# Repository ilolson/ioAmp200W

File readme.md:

# ioAmp200W

Small but powerful USB-C powered two channel speaker amplifier.

# Summary

Integrating the MA5332MS from infineon, a super efficient and compact 2 channel class D amplifier. With a TLV320AIC3254 mini DSP, a low power and compact DSP for consumer audio applications that will allow for tight integration. TPS26750 to control USB PD 3.1 EPR power supplies for up to 240W of DC power. An easy to use RP2350 microcontroller for high level control of the system, and hopefully digital audio in at 24bit/96khz.

The goal is to design a compact and efficient circuit board that can supply a wide range of power to the class D amplifier through USB-C Power Delivery. It will include line in and out for easy audio amplification. Including a quality and easy to use DSP such as the TLV320AIC3254 mini DSP should allow us to explore signal processing techniques to achieve optimal results at different power supply voltages, and different speaker setups. Digital audio in over USB-C should be possible in the future with the RP2350 and the DSP. For fun we can drive a HUB75 matrix panel in real time using existing optimized libraries with our signal.

# Power Supply

The USB PD 3.1 EPR can supply a maximum of 48V@5A for 240 watts DC. Even lower settings such as 20V/3A is a common laptop charging standard and many people already own USB-C bricks that can supply this which should be enough for some decent audio output, it also won't damage anything so it will be a safe default. The highest easily available is 28V@5A for 140W DC. 48V@5A is hard to find and expensive although I do plan on testing it on the first revision. 

# Major Circuits

-RP2350 microcontroller

-TI TPS26750 PD 3.1 EPR controller and power management system

-MA5332MS class D amplifier (up to 100W/Ch without heatsink)

-TLV3254AIC3254 low power consumer audio codec DSP, digital input from RP2350 and analog line in

# Highlights

-USB-C digital audio in (24 bit/96kHz)

-Program/Serial connectivity available while streaming audio over USB for easy real time DSP control

-Line In

-HUB75 interface (for driving LED matrix panels)

-High quality audio amplification at a manageable cost for DIY setups

-Wide range of easily available power supplies

# Status

-Initial schematic design

-Compilable firmware, serial and digital audio in working

-Auto install toolchain and compile scripts

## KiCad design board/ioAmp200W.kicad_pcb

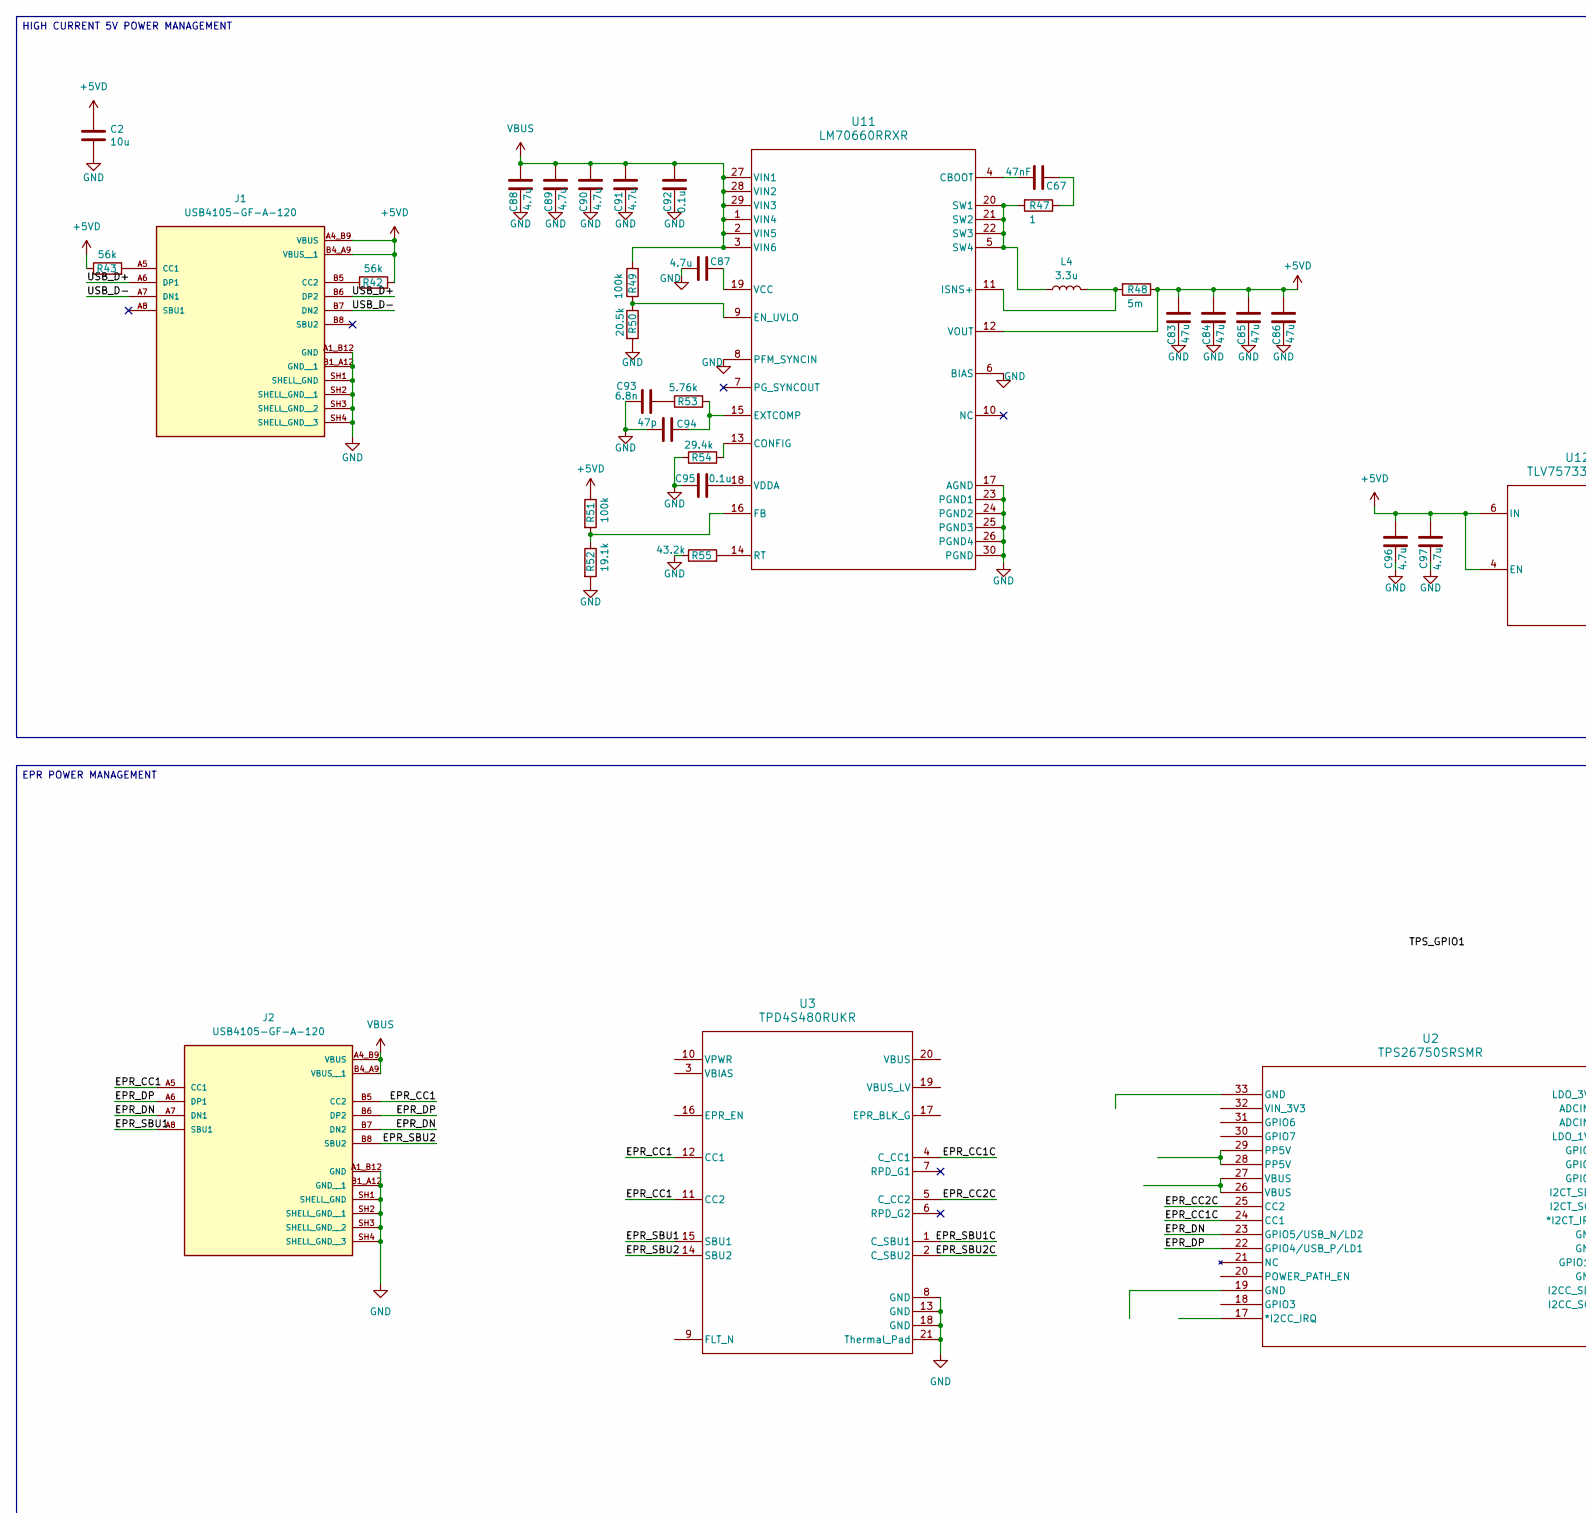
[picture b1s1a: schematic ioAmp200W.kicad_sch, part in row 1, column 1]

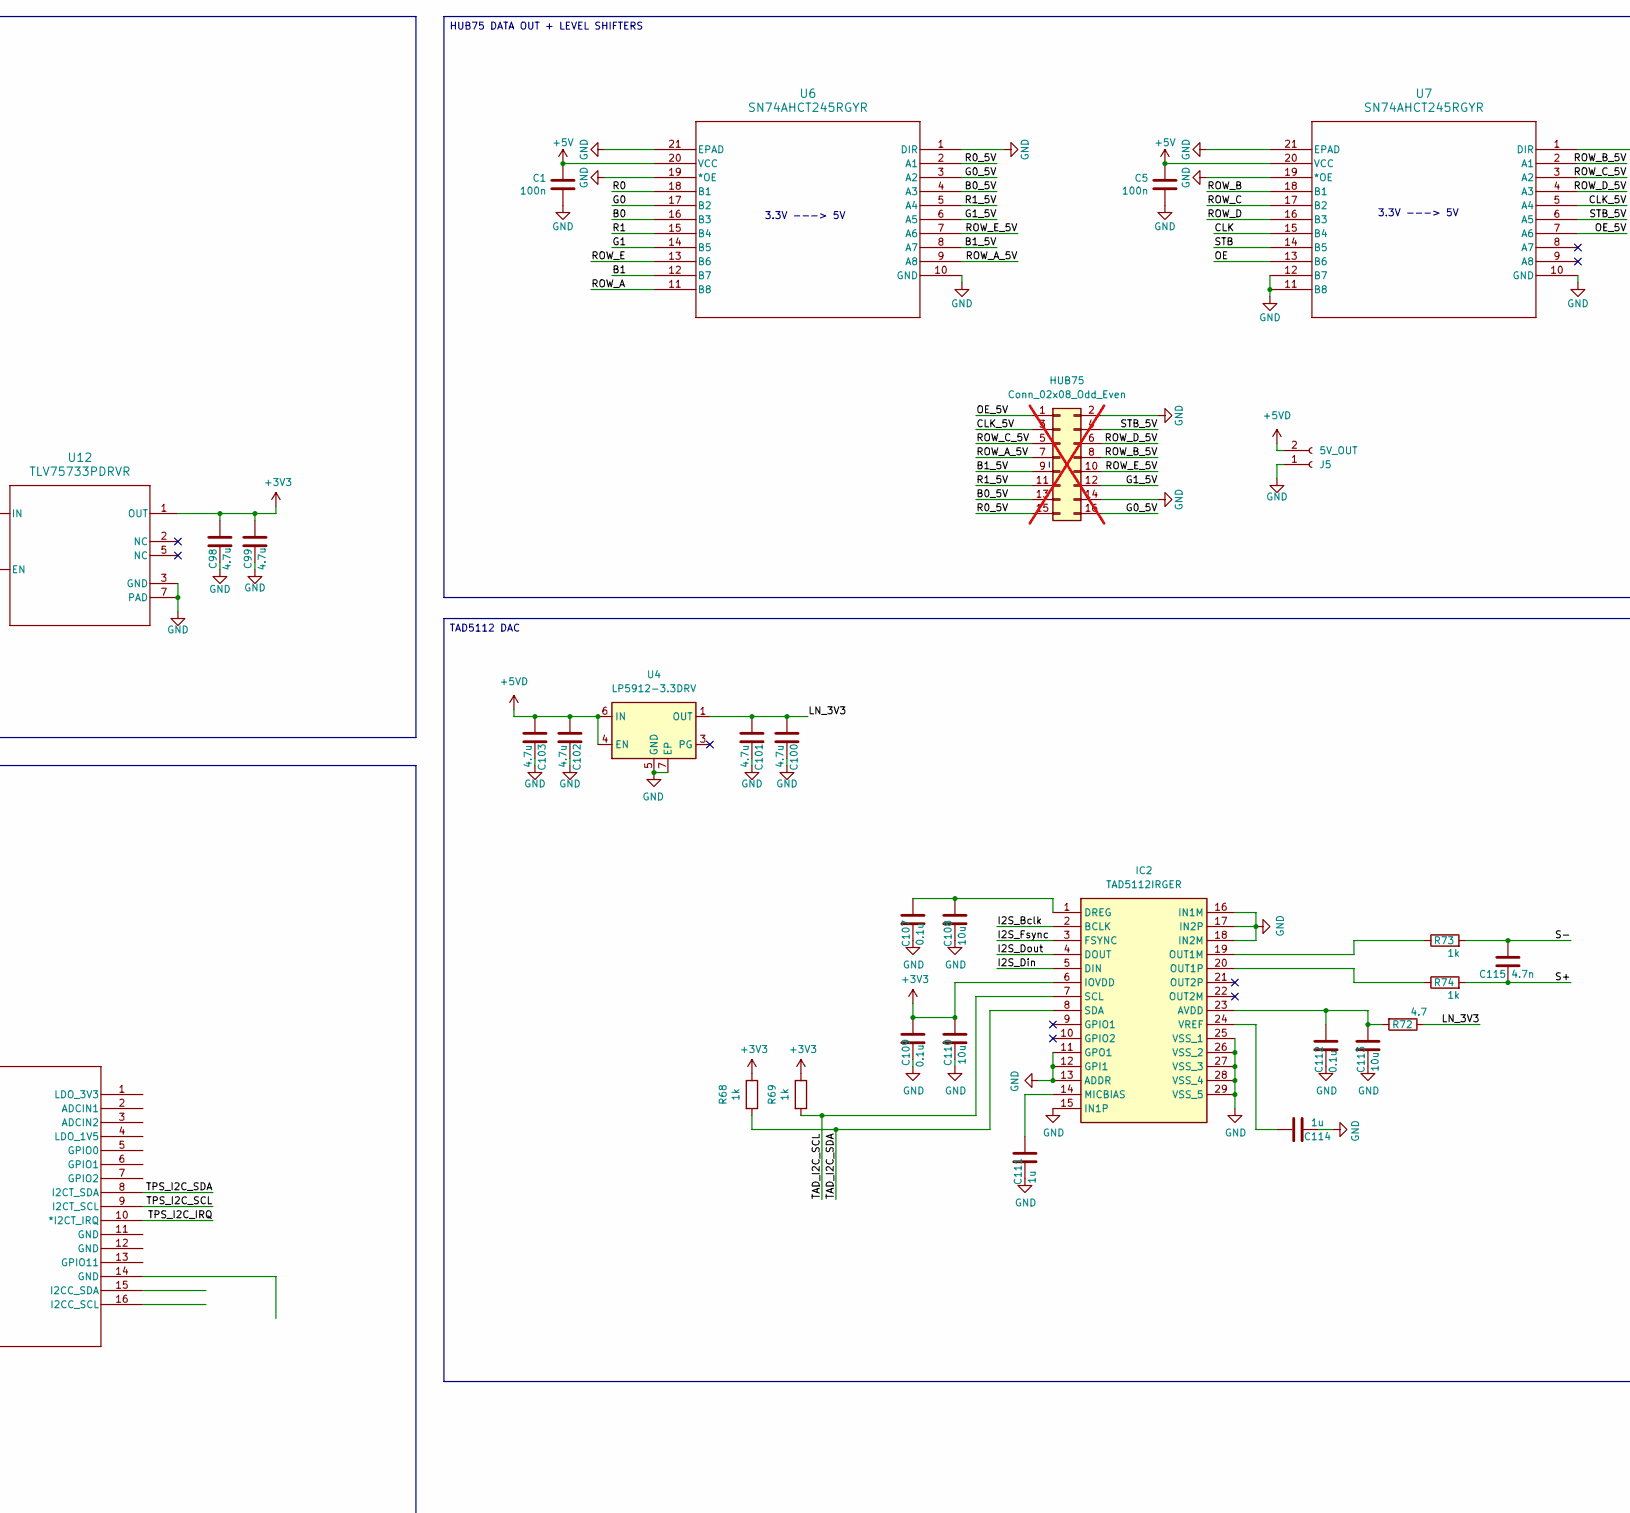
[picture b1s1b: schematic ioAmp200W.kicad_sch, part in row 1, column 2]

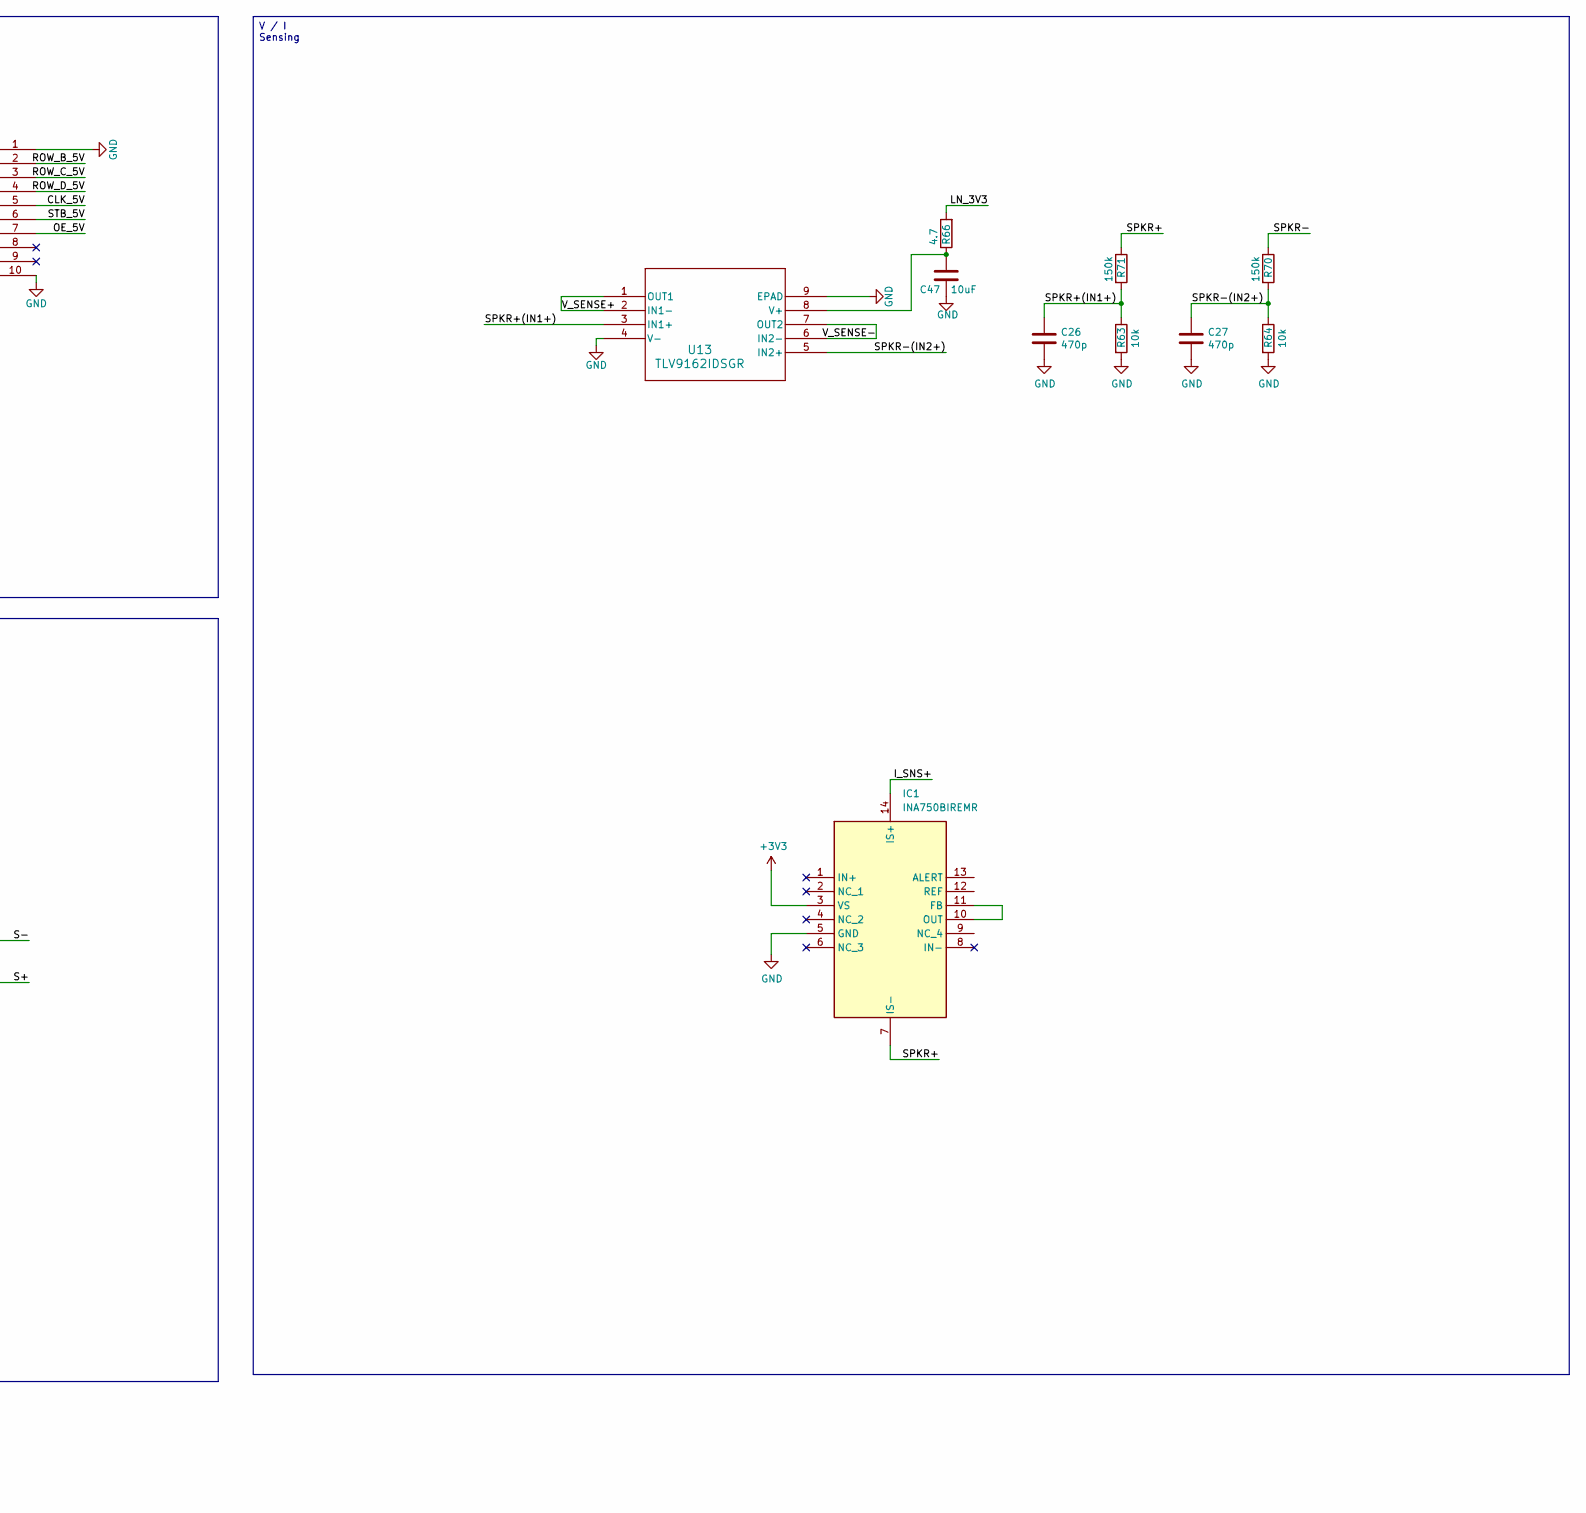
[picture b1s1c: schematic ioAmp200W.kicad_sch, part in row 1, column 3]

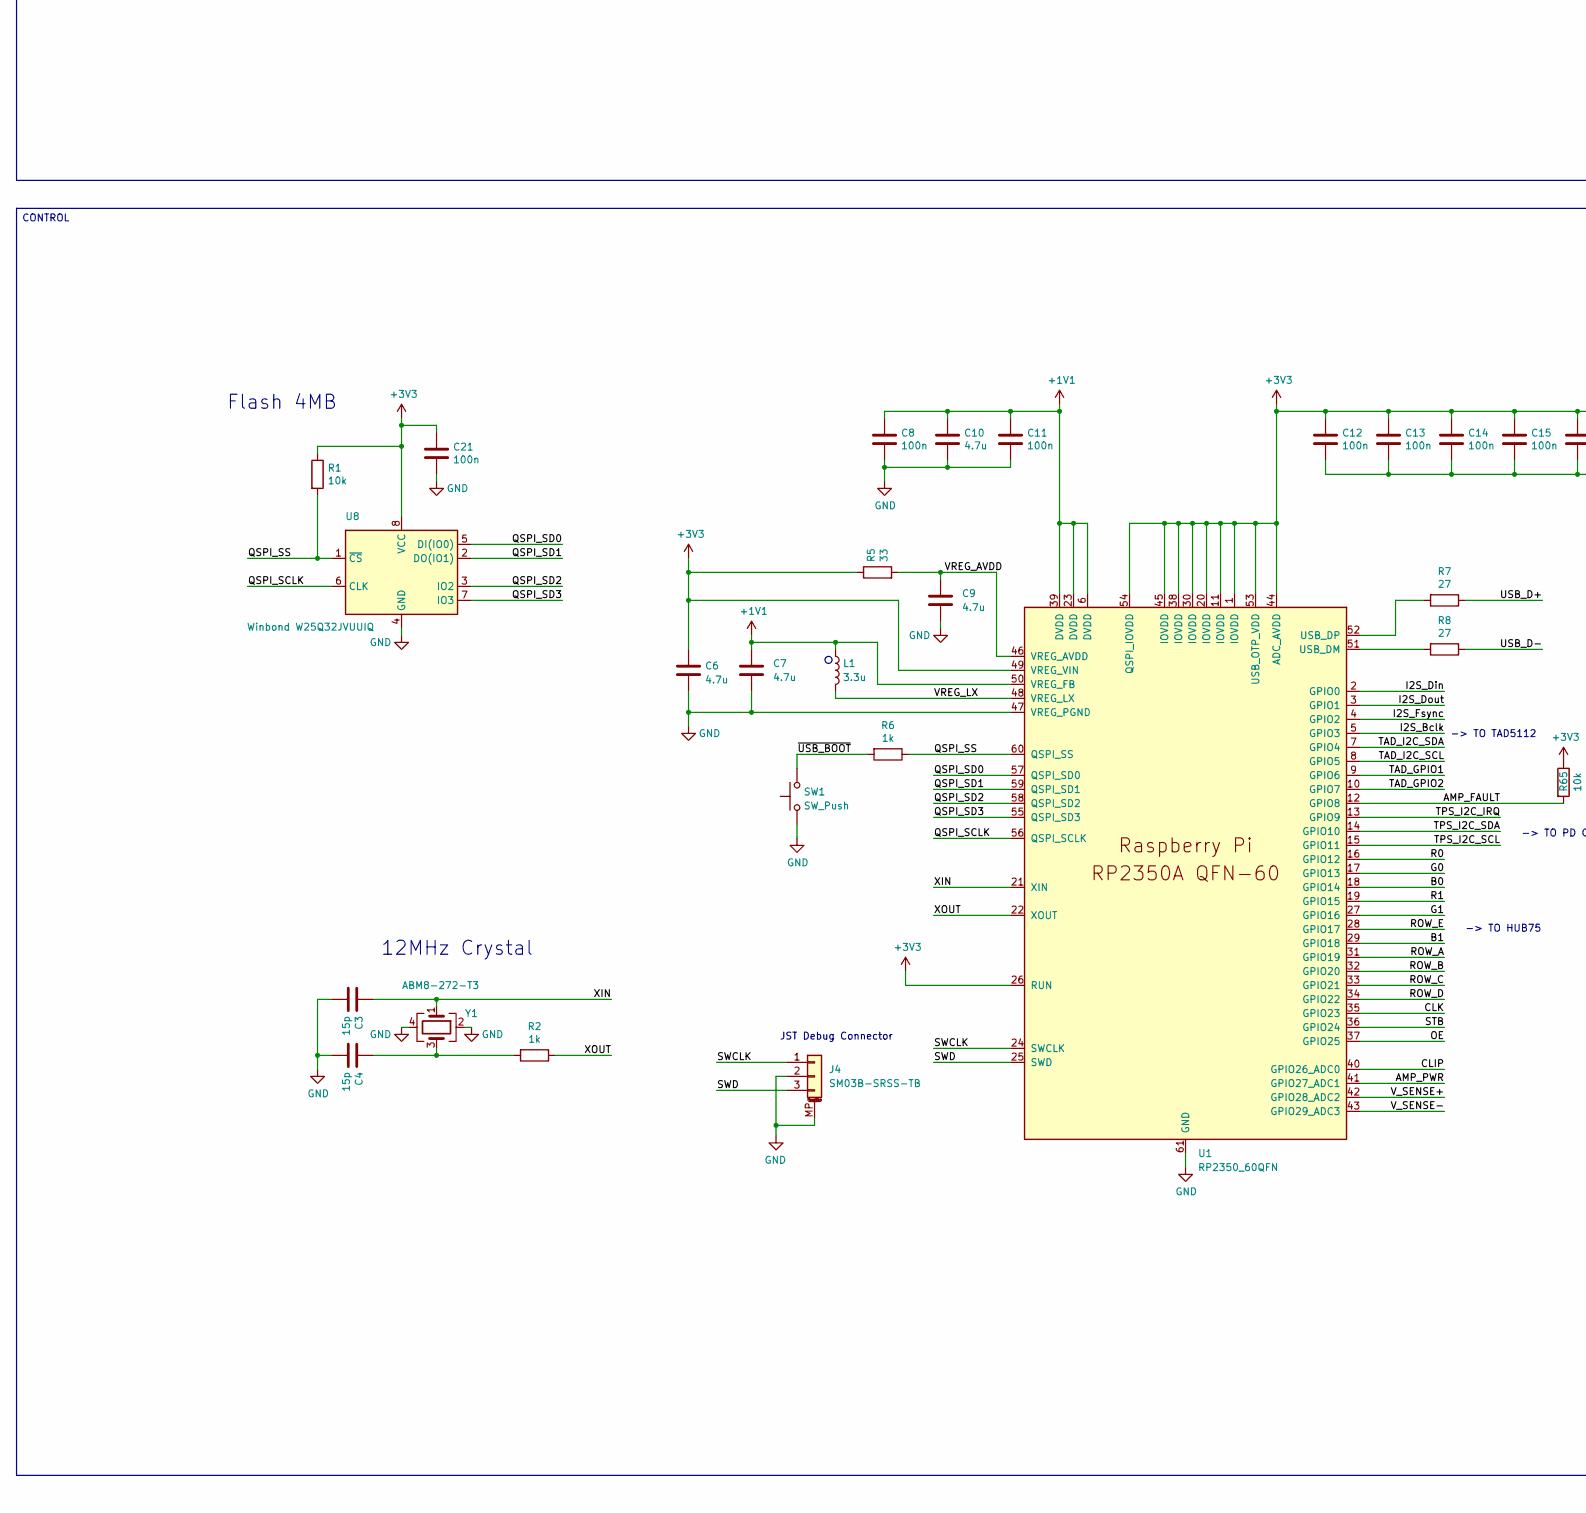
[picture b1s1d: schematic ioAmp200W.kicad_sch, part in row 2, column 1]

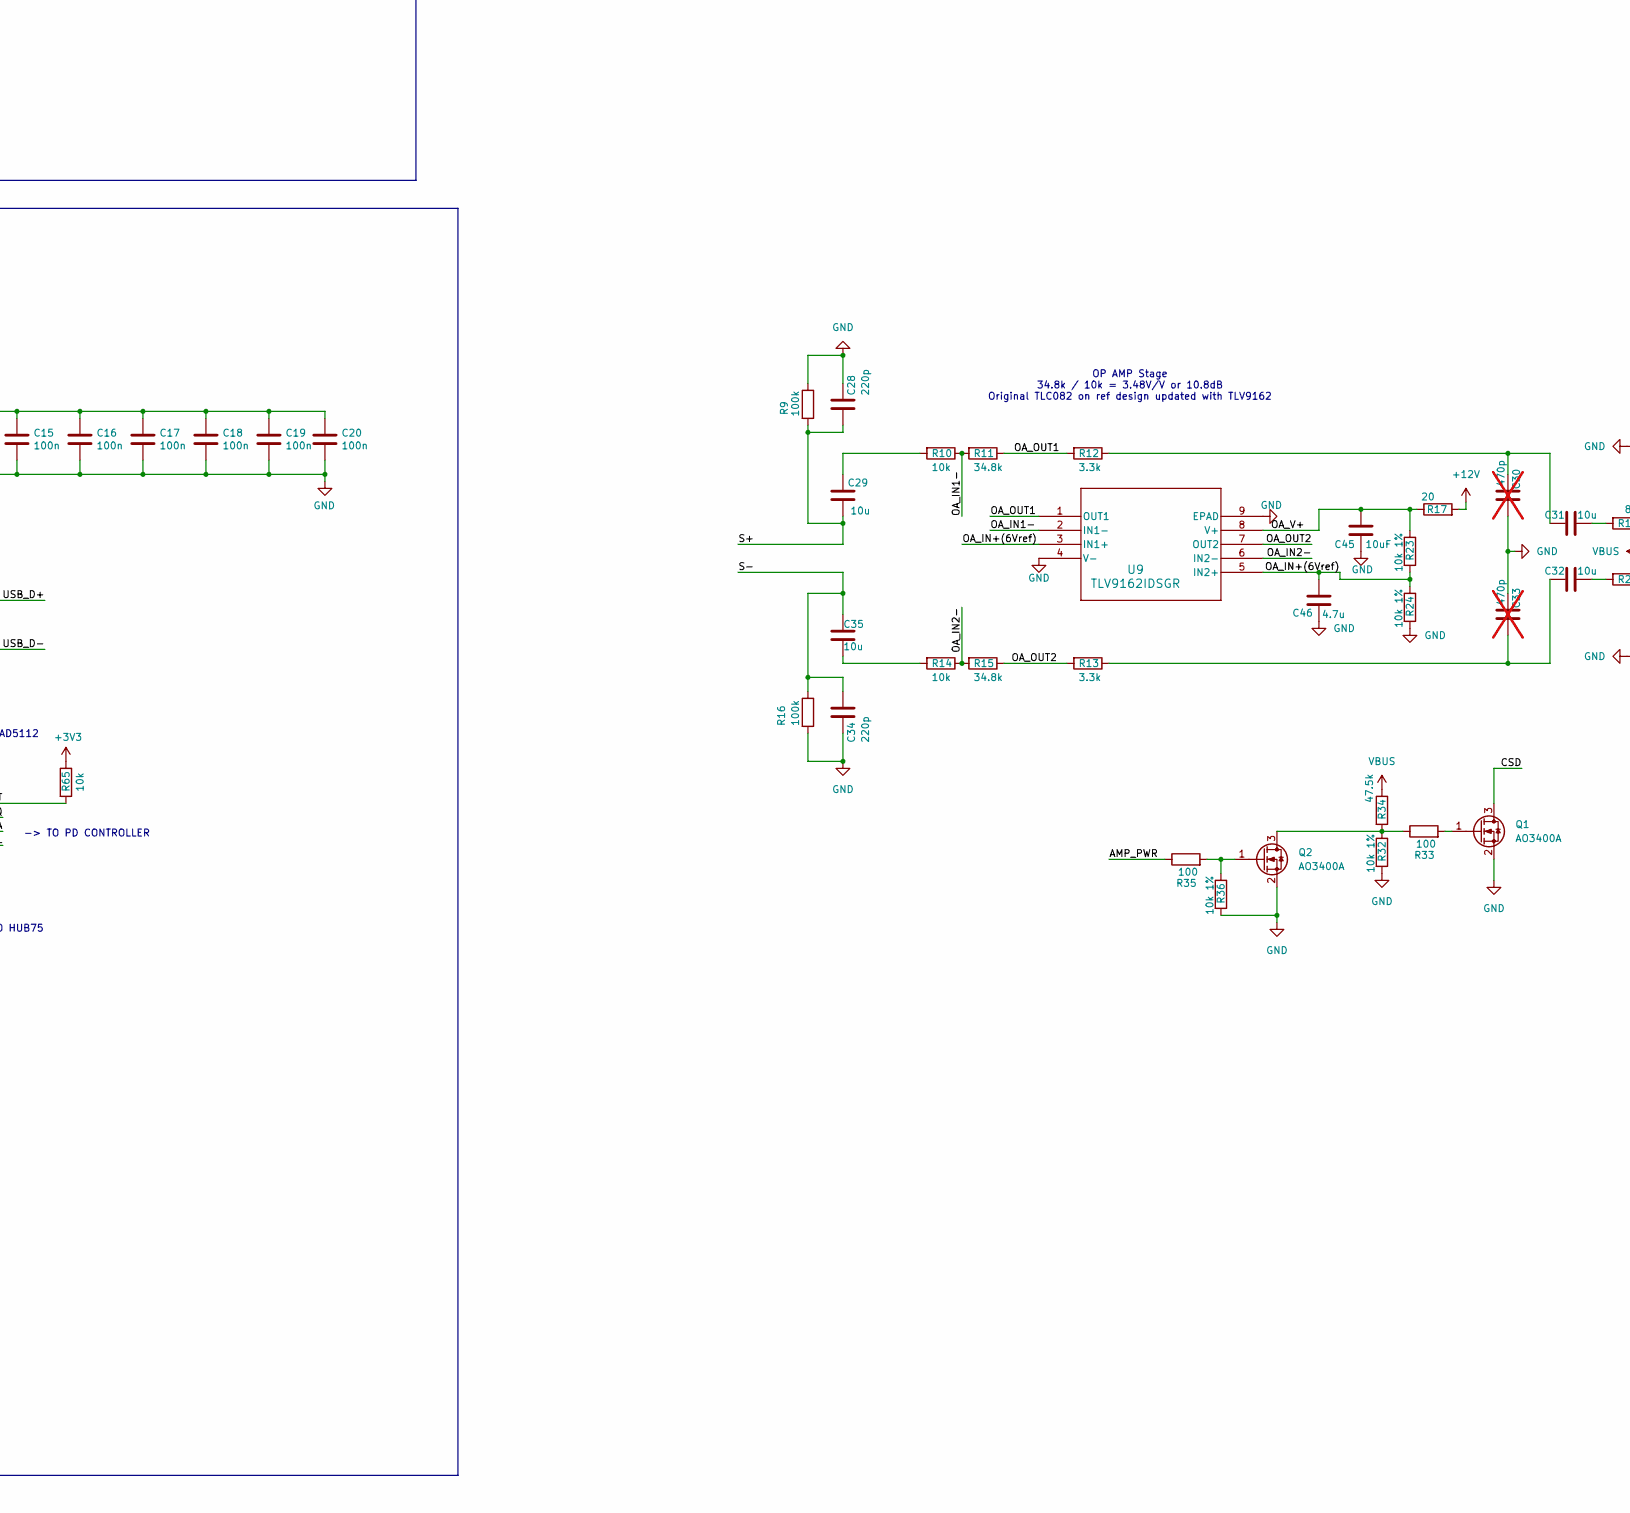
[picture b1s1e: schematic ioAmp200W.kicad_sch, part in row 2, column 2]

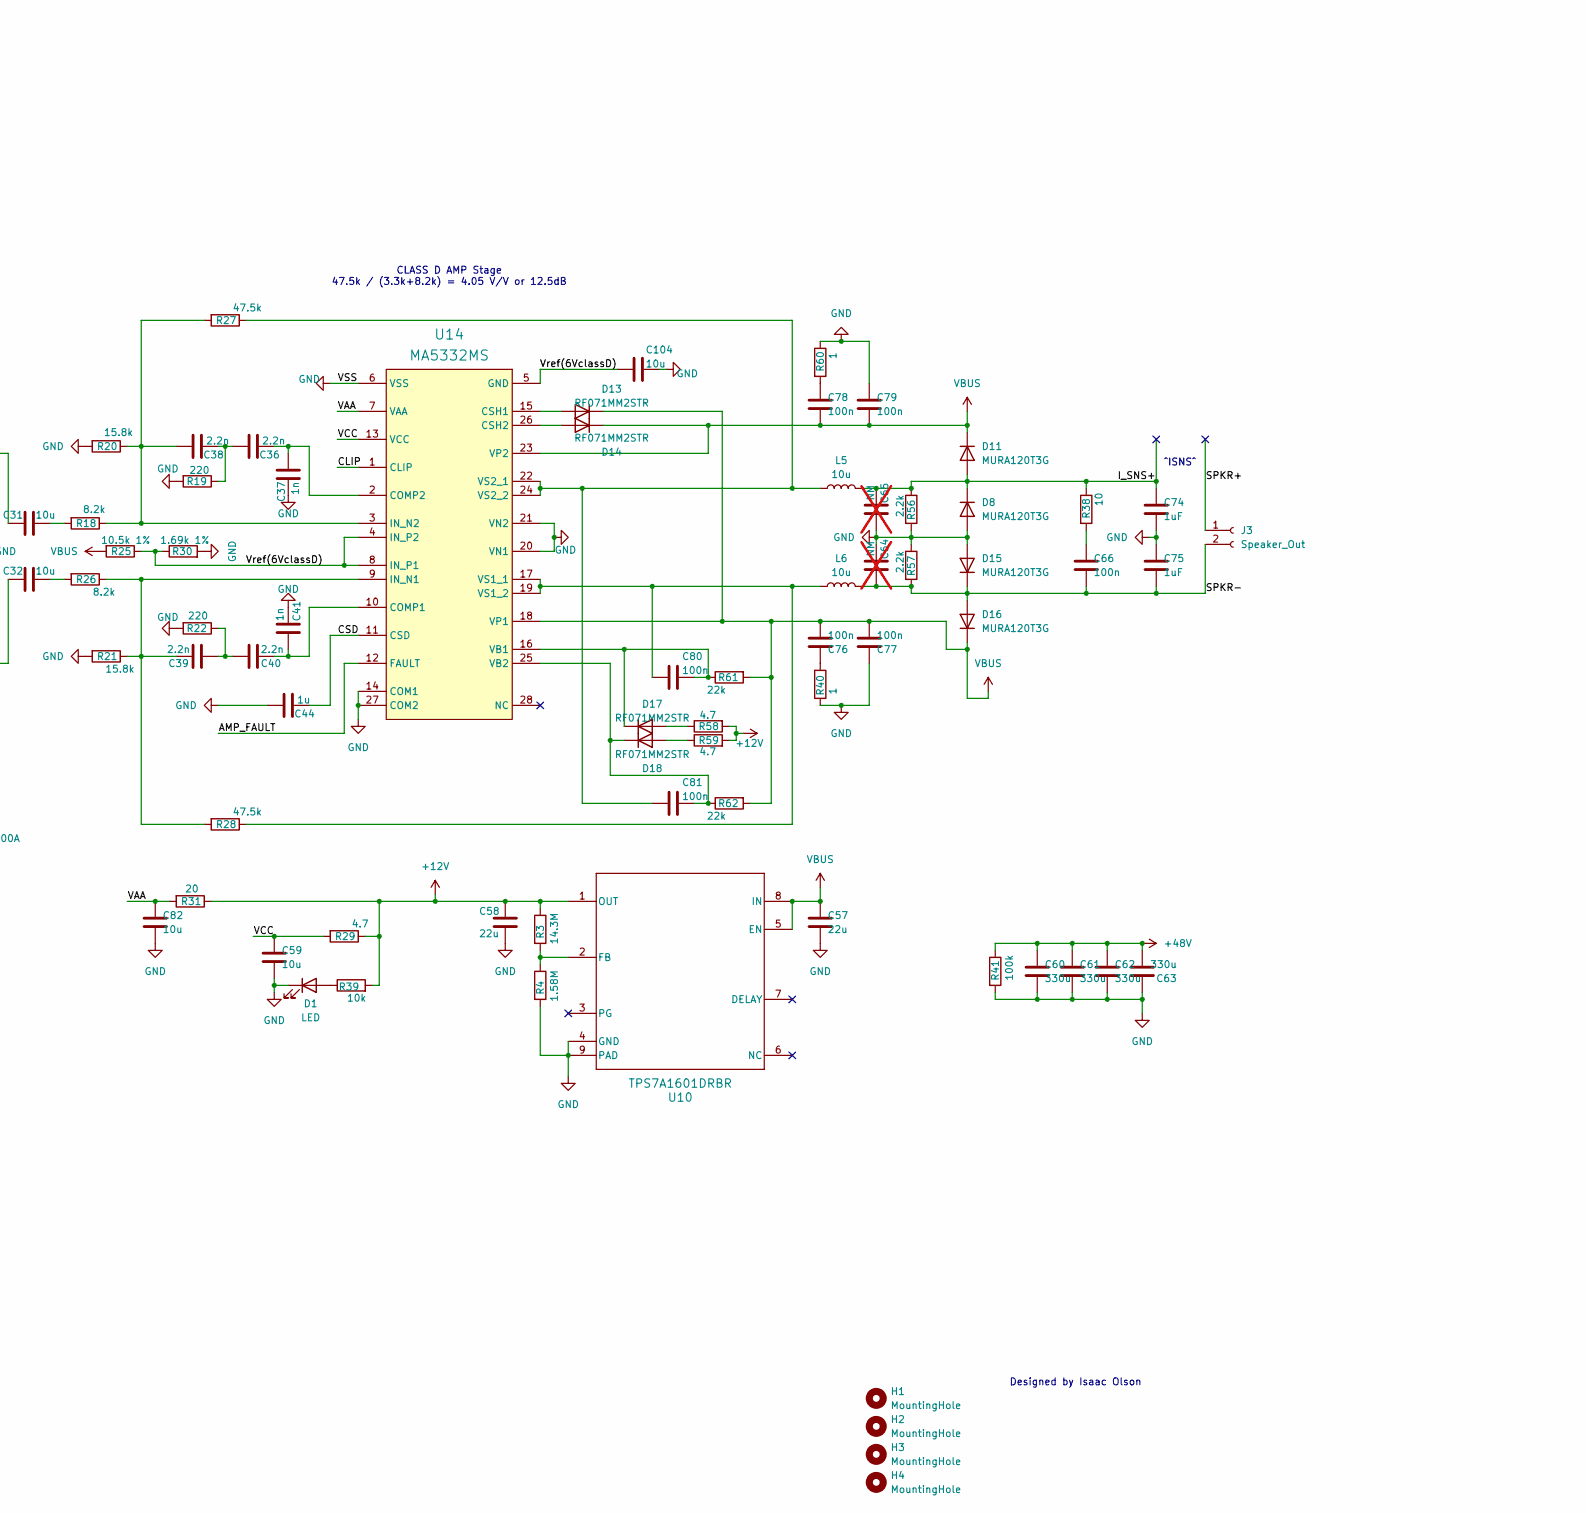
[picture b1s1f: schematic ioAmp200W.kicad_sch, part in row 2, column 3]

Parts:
C1, C5, C8, C11, C12, C13, C14, C15, C16, C17, C18, C19, C20, C21, C66, C76, C77, C78, C79, C80, C81: 100n; C_0402_1005Metric
C2, C29, C31, C32, C35, C59, C82, C104, C108, C110, C113: 10u; C_0402_1005Metric
C3, C4: 15p; C_0402_1005Metric
C6, C7, C9, C10, C46: 4.7u; C_0402_1005Metric
C26, C27: 470p; C_0402_1005Metric
C28, C34: 220p; C_0402_1005Metric
C30, C33: 470p; C_0402_1005Metric; not fitted
C36, C38, C39, C40: 2.2n; C_0402_1005Metric
C37, C41: 1n; C_0402_1005Metric
C44, C111, C114: 1u; C_0402_1005Metric
C45, C47: 10uF; C_0402_1005Metric
C57, C58: 22u; C_0402_1005Metric
C60, C61, C62, C63: 330u; C_0402_1005Metric
C64, C65: NM; C_0402_1005Metric; not fitted
C67: 47nF; C_0402_1005Metric
C74, C75: 1uF
C83, C84, C85, C86: 47u; C_1210_3225Metric; LCSC C440151
C87, C88, C89, C90, C96, C98, C100, C102: 4.7u; C_1210_3225Metric; LCSC C913445
C91, C97, C99, C101, C103: 4.7u; C_1210_3225Metric
C92, C95, C107, C109, C112: 0.1u; C_0402_1005Metric
C93: 6.8n; C_0402_1005Metric
C94: 47p; C_0402_1005Metric
C115: 4.7n; C_0402_1005Metric
D1: LED; LED_0402_1005Metric
D8, D11, D15, D16: MURA120T3G; D_SMA; LCSC C111832
D13, D14, D17, D18: RF071MM2STR; D_SOD-123; LCSC C253520
H1, H2, H3, H4: MountingHole; MountingHole_2.1mm
HUB75: Conn_02x08_Odd_Even; IDC-Header_2x08_P2.54mm_Vertical_SMD; not fitted
IC1: INA750BIREMR; INA740BIREMR; Manufacturer_Part_Number INA750BIREMR
IC2: TAD5112IRGER; Manufacturer_Part_Number TAD5112IRGER
J1, J2: USB4105-GF-A-120; GCT_USB4105-GF-A-120; PARTREV B3
J3: Speaker_Out; AMASS_XT30U-F_1x02_P5.0mm_Vertical
J4: SM03B-SRSS-TB; JST_SH_SM03B-SRSS-TB_1x03-1MP_P1.00mm_Horizontal
J5: 5V_OUT; AMASS_XT30U-F_1x02_P5.0mm_Vertical
L1: 3.3u; L_pol_2016
L4: 3.3u; L_Bourns_SRP7028A_7.3x6.6mm; LCSC C3040366
L5, L6: 10u; C_0402_1005Metric
Q1, Q2: AO3400A; SOT-23; LCSC C347475
R1, R10, R14, R39, R63, R64, R65: 10k; R_0402_1005Metric
R2, R6, R68, R69, R73, R74: 1k; R_0402_1005Metric
R3: 14.3M; R_0402_1005Metric
R4: 1.58M; R_0402_1005Metric
R5: 33; R_0402_1005Metric
R7, R8: 27; R_0402_1005Metric
R9, R16, R41, R49, R51: 100k; R_0402_1005Metric
R11, R15: 34.8k; R_0402_1005Metric
R12, R13: 3.3k; R_0402_1005Metric
R17, R31: 20; R_0402_1005Metric
R18, R26: 8.2k; R_0402_1005Metric
R19, R22: 220; R_0402_1005Metric
R20, R21: 15.8k; R_0402_1005Metric
R23, R24, R32, R36: 10k 1%; R_0402_1005Metric
R25: 10.5k 1%; R_0402_1005Metric
R27, R28, R34: 47.5k; R_0402_1005Metric
R29, R58, R59, R66, R72: 4.7; R_0402_1005Metric
R30: 1.69k 1%; R_0402_1005Metric
R33, R35: 100; R_0402_1005Metric
R38: 10; R_0402_1005Metric
R40, R47, R60: 1; R_0402_1005Metric
R42, R43: 56k; R_0402_1005Metric
R48: 5m; R_1206_3216Metric; LCSC C6973817
R50: 20.5k; R_0402_1005Metric
R52: 19.1k; R_0402_1005Metric
R53: 5.76k; R_0402_1005Metric
R54: 29.4k; R_0402_1005Metric
R55: 43.2k; R_0402_1005Metric
R56, R57: 2.2k; R_0402_1005Metric
R61, R62: 22k; R_0402_1005Metric
R70, R71: 150k; R_0402_1005Metric
SW1: SW_Push; SW_SPST_TS-1088-xR020; LCSC C720477
U1: RP2350_60QFN; RP2350-QFN-60-1EP_7x7_P0.4mm_EP3.4x3.4mm_ThermalVias
U2: TPS26750SRSMR; VQFN32_RSM_TEX-L
U3: TPD4S480RUKR; RUK0020B-MFG
U4: LP5912-3.3DRV; WSON-6-1EP_2x2mm_P0.65mm_EP1x1.6mm
U6, U7: SN74AHCT245RGYR; DHVQFN-20-1EP_2.5x4.5mm_P0.5mm_EP1x3mm
U8: Winbond W25Q32JVUUIQ; Winbond_USON-8-2EP_3x4mm_P0.8mm_EP0.2x0.8mm; LCSC C2999380
U9, U13: TLV9162IDSGR; WSON8_DSG_TEX
U10: TPS7A1601DRBR; DRB0008B
U11: LM70660RRXR; RRX0029B-MFG
U12: TLV75733PDRVR; DRV0006A_NV
U14: MA5332MS; IFX-PG-IQFN-42-1-V
Y1: ABM8-272-T3; Crystal_SMD_3225-4Pin_3.2x2.5mm

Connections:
+1V1: C7.1, C8.1, C10.1, C11.1, L1.1, U1.6 (DVDD), U1.23 (DVDD), U1.39 (DVDD), U1.50 (VREG_FB)
+3V3: C6.1, C12.1, C13.1, C14.1, C15.1, C16.1, C17.1, C18.1, C19.1, C20.1, C21.1, C98.1, C99.1, C109.1, C110.1, IC1.3 (VS), IC2.6 (IOVDD), R1.1, R5.1, R65.1, R68.1, R69.1, U1.1 (IOVDD), U1.11 (IOVDD), U1.20 (IOVDD), U1.26 (RUN), U1.30 (IOVDD), U1.38 (IOVDD), U1.44 (ADC_AVDD), U1.45 (IOVDD), U1.49 (VREG_VIN), U1.53 (USB_OTP_VDD), U1.54 (QSPI_IOVDD), U8.8 (VCC), U12.1 (OUT)
+5V: C1.1, C5.1, U6.20 (VCC), U7.20 (VCC)
+5VD: C2.1, C83.1, C84.1, C85.1, C86.1, C96.1, C97.1, C102.1, C103.1, J1.A4_B9 (VBUS), J1.B4_A9 (VBUS__1), J5.2, R42.2, R43.1, R48.1, R51.1, U4.4 (EN), U4.6 (IN), U11.12 (VOUT), U12.4 (EN), U12.6 (IN)
+12V: C58.2, R3.1, R17.2, R29.1, R31.1, R39.2, R58.2, R59.2, U10.1 (OUT)
+48V: C60.2, C61.2, C62.2, C63.2, R41.1
/AMP_FAULT: R65.2, U1.12 (GPIO8), U14.12 (FAULT)
/AMP_PWR: R35.1, U1.41 (GPIO27_ADC1)
/B0: U1.18 (GPIO14), U6.16 (B3)
/B0_5V: HUB75.13, U6.4 (A3)
/B1: U1.29 (GPIO18), U6.12 (B7)
/B1_5V: HUB75.9, U6.8 (A7)
/CLIP: U1.40 (GPIO26_ADC0), U14.1 (CLIP)
/CLK: U1.35 (GPIO23), U7.15 (B4)
/CLK_5V: HUB75.3, U7.5 (A4)
/CSD: C44.1, Q1.3 (D), U14.11 (CSD)
/EPR_CC1: J2.A5 (CC1), J2.B5 (CC2), U3.11 (CC2), U3.12 (CC1)
/EPR_CC1C: U2.24 (CC1), U3.4 (C_CC1)
/EPR_CC2C: U2.25 (CC2), U3.5 (C_CC2)
/EPR_DN: J2.A7 (DN1), J2.B7 (DN2), U2.23 (GPIO5/USB_N/LD2)
/EPR_DP: J2.A6 (DP1), J2.B6 (DP2), U2.22 (GPIO4/USB_P/LD1)
/EPR_SBU1: J2.A8 (SBU1), U3.15 (SBU1)
/EPR_SBU1C: U3.1 (C_SBU1)
/EPR_SBU2: J2.B8 (SBU2), U3.14 (SBU2)
/EPR_SBU2C: U3.2 (C_SBU2)
/G0: U1.17 (GPIO13), U6.17 (B2)
/G0_5V: HUB75.16, U6.3 (A2)
/G1: U1.27 (GPIO16), U6.14 (B5)
/G1_5V: HUB75.12, U6.6 (A5)
/I2S_Bclk: IC2.2 (BCLK), U1.5 (GPIO3)
/I2S_Din: IC2.5 (DIN), U1.2 (GPIO0)
/I2S_Dout: IC2.4 (DOUT), U1.3 (GPIO1)
/I2S_Fsync: IC2.3 (FSYNC), U1.4 (GPIO2)
/LN_3V3: C100.1, C101.1, R66.2, R72.1, U4.1 (OUT)
/OA_IN1-: R10.1, R11.2, U9.2 (IN1-)
/OA_IN2-: R14.1, R15.2, U9.6 (IN2-)
/OA_IN+(6Vref): C46.2, R23.2, R24.1, U9.3 (IN1+), U9.5 (IN2+)
/OA_OUT1: R11.1, R12.2, U9.1 (OUT1)
/OA_OUT2: R13.2, R15.1, U9.7 (OUT2)
/OA_V+: C45.2, R17.1, R23.1, U9.8 (V+)
/OE: U1.37 (GPIO25), U7.13 (B6)
/OE_5V: HUB75.1, U7.7 (A6)
/QSPI_SCLK: U1.56 (QSPI_SCLK), U8.6 (CLK)
/QSPI_SD0: U1.57 (QSPI_SD0), U8.5 (DI(IO0))
/QSPI_SD1: U1.59 (QSPI_SD1), U8.2 (DO(IO1))
/QSPI_SD2: U1.58 (QSPI_SD2), U8.3 (IO2)
/QSPI_SD3: U1.55 (QSPI_SD3), U8.7 (IO3)
/QSPI_SS: R1.2, R6.1, U1.60 (QSPI_SS), U8.1 (~CS)
/R0: U1.16 (GPIO12), U6.18 (B1)
/R0_5V: HUB75.15, U6.2 (A1)
/R1: U1.19 (GPIO15), U6.15 (B4)
/R1_5V: HUB75.11, U6.5 (A4)
/ROW_A: U1.31 (GPIO19), U6.11 (B8)
/ROW_A_5V: HUB75.7, U6.9 (A8)
/ROW_B: U1.32 (GPIO20), U7.18 (B1)
/ROW_B_5V: HUB75.8, U7.2 (A1)
/ROW_C: U1.33 (GPIO21), U7.17 (B2)
/ROW_C_5V: HUB75.5, U7.3 (A2)
/ROW_D: U1.34 (GPIO22), U7.16 (B3)
/ROW_D_5V: HUB75.6, U7.4 (A3)
/ROW_E: U1.28 (GPIO17), U6.13 (B6)
/ROW_E_5V: HUB75.10, U6.7 (A6)
/S+: C28.2, C29.2, C115.2, R9.2, R74.2
/S-: C34.1, C35.1, C115.1, R16.1, R73.2
/SENSE+: U1.42 (GPIO28_ADC2), U13.1 (OUT1), U13.2 (IN1-)
/SENSE-: U1.43 (GPIO29_ADC3), U13.6 (IN2-), U13.7 (OUT2)
/SPKR+(IN1+): C26.1, R63.1, R71.2, U13.3 (IN1+)
/SPKR-: C64.2, C66.1, C75.1, D15.1 (K), D16.2 (A), J3.2, L6.2, R57.2, R70.1
/SPKR-(IN2+): C27.1, R64.1, R70.2, U13.5 (IN2+)
/STB: U1.36 (GPIO24), U7.14 (B5)
/STB_5V: HUB75.4, U7.6 (A5)
/SWCLK: J4.1, U1.24 (SWCLK)
/SWD: J4.3, U1.25 (SWD)
/TAD_GPIO1: U1.9 (GPIO6)
/TAD_GPIO2: U1.10 (GPIO7)
/TAD_I2C_SCL: IC2.7 (SCL), R69.2, U1.8 (GPIO5)
/TAD_I2C_SDA: IC2.8 (SDA), R68.2, U1.7 (GPIO4)
/TPS_I2C_IRQ: U1.13 (GPIO9), U2.10 (*I2CT_IRQ)
/TPS_I2C_SCL: U1.15 (GPIO11), U2.9 (I2CT_SCL)
/TPS_I2C_SDA: U1.14 (GPIO10), U2.8 (I2CT_SDA)
/USB_D+: J1.A6 (DP1), J1.B6 (DP2), R7.1
/USB_D-: J1.A7 (DN1), J1.B7 (DN2), R8.1
/VAA: C82.2, R31.2, U14.7 (VAA)
/VCC: C59.2, R29.2, U14.13 (VCC)
/VREG_AVDD: C9.1, R5.2, U1.46 (VREG_AVDD)
/VREG_LX: L1.2, U1.48 (VREG_LX)
/Vref(6VclassD): C104.1, R25.1, R30.1, U14.4 (IN_P2), U14.5 (GND), U14.8 (IN_P1)
/XIN: C3.1, U1.21 (XIN), Y1.1
/XOUT: R2.1, U1.22 (XOUT)
/~USB_BOOT: R6.2, SW1.2
GND: C1.2, C2.2, C3.2, C4.2, C5.2, C6.2, C7.2, C8.2, C9.2, C10.2, C11.2, C12.2, C13.2, C14.2, C15.2, C16.2, C17.2, C18.2, C19.2, C20.2, C21.2, C26.2, C27.2, C28.1, C30.2, C33.1, C34.2, C37.2, C41.1, C44.2, C45.1, C46.1, C47.1, C57.1, C58.1, C59.1, C60.1, C61.1, C62.1, C63.1, C64.1, C65.2, C74.1, C75.2, C77.2, C79.2, C82.1, C83.2, C84.2, C85.2, C86.2, C87.2, C88.2, C89.2, C90.2, C91.2, C92.2, C93.2, C94.2, C95.2, C96.2, C97.2, C98.2, C99.2, C100.2, C101.2, C102.2, C103.2, C104.2, C107.2, C108.2, C109.2, C110.2, C111.2, C112.2, C113.2, C114.2, D1.1 (K), D8.2 (A), D15.2 (A), HUB75.2, HUB75.14, IC1.5 (GND), IC2.11 (GPO1), IC2.12 (GPI1), IC2.13 (ADDR), IC2.15 (IN1P), IC2.16 (IN1M), IC2.17 (IN2P), IC2.18 (IN2M), IC2.25 (VSS_1), IC2.26 (VSS_2), IC2.27 (VSS_3), IC2.28 (VSS_4), IC2.29 (VSS_5), J1.A1_B12 (GND), J1.B1_A12 (GND__1), J1.SH1 (SHELL_GND), J1.SH2 (SHELL_GND__1), J1.SH3 (SHELL_GND__2), J1.SH4 (SHELL_GND__3), J2.A1_B12 (GND), J2.B1_A12 (GND__1), J2.SH1 (SHELL_GND), J2.SH2 (SHELL_GND__1), J2.SH3 (SHELL_GND__2), J2.SH4 (SHELL_GND__3), J4.2, J4.MP (MountPin), J5.1, Q1.2 (S), Q2.2 (S), R4.2, R9.1, R16.2, R19.2, R20.2, R21.2, R22.2, R24.2, R30.2, R32.2, R36.2, R40.1, R41.2, R50.2, R52.2, R54.1, R55.1, R56.2, R57.1, R60.1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; also elsewhere on the board
unnamed: C4.1, R2.2, Y1.3
unnamed: C29.1, R10.2
unnamed: C30.1, C31.1, R12.1
unnamed: C31.2, R18.2
unnamed: C32.1, C33.2, R13.1
unnamed: C32.2, R26.2
unnamed: C35.2, R14.2
unnamed: C36.2, C38.1, R19.1
unnamed: C39.1, C40.2, R22.1
unnamed: C66.2, R38.2
unnamed: C67.1, R47.1
unnamed: C76.2, R40.2
unnamed: C78.2, R60.2
unnamed: C93.1, R53.1
unnamed: D1.2 (A), R39.1
unnamed: D13.2 (A), U14.15 (CSH1)
unnamed: D14.2 (A), U14.26 (CSH2)
unnamed: D17.2 (A), R58.1
unnamed: C80.2, D17.1 (K), R61.1, U14.16 (VB1)
unnamed: D18.2 (A), R59.1
unnamed: C81.2, D18.1 (K), R62.1, U14.25 (VB2)
unnamed: C112.1, C113.1, IC2.23 (AVDD), R72.2
unnamed: C107.1, C108.1, IC2.1 (DREG)
unnamed: C111.1, IC2.14 (MICBIAS)
unnamed: IC2.19 (OUT1M), R73.1
unnamed: IC2.20 (OUT1P), R74.1
unnamed: C114.1, IC2.24 (VREF)
unnamed 118: J1.A5 (CC1), R43.2; also elsewhere on the board
unnamed 119: J1.B5 (CC2), R42.1; also elsewhere on the board
unnamed: Q1.1 (G), R33.2
unnamed: Q2.3 (D), R32.1, R33.1, R34.2
unnamed: Q2.1 (G), R35.2, R36.1
unnamed: R8.2, U1.51 (USB_DM)
unnamed: R7.2, U1.52 (USB_DP)
unnamed: U2.28 (PP5V), U2.29 (PP5V)
unnamed: U2.26 (VBUS), U2.27 (VBUS)
unnamed: R3.2, R4.1, U10.2 (FB)
unnamed: C67.2, U11.4 (CBOOT)
unnamed: R54.2, U11.13 (CONFIG)
unnamed: R49.1, R50.1, U11.9 (EN_UVLO)
unnamed: C94.1, R53.2, U11.15 (EXTCOMP)
unnamed: R51.2, R52.1, U11.16 (FB)
unnamed: L4.2, R48.2, U11.11 (ISNS+)
unnamed: R55.2, U11.14 (RT)
unnamed: L4.1, R47.2, U11.5 (SW4), U11.20 (SW1), U11.21 (SW2), U11.22 (SW3)
unnamed: C87.1, U11.19 (VCC)
unnamed: C95.1, U11.18 (VDDA)
unnamed: C47.2, R66.1, U13.8 (V+)
unnamed: C40.1, C41.2, U14.10 (COMP1)
unnamed: C36.1, C37.1, U14.2 (COMP2)
unnamed: C39.2, R21.1, R26.1, R28.2, U14.9 (IN_N1)
unnamed: C38.2, R18.1, R20.1, R27.2, U14.3 (IN_N2)
unnamed: C80.1, L6.1, R28.1, U14.17 (VS1_1), U14.19 (VS1_2)
unnamed: C81.1, L5.1, R27.1, U14.22 (VS2_1), U14.24 (VS2_2)
VBUS: C57.2, C76.1, C77.1, C78.1, C79.1, C88.1, C89.1, C90.1, C91.1, C92.1, D11.1 (K), D13.1 (K), D14.1 (K), D16.1 (K), J2.A4_B9 (VBUS), J2.B4_A9 (VBUS__1), R25.2, R34.1, R49.2, R61.2, R62.2, U10.5 (EN), U10.8 (IN), U11.1 (VIN4), U11.2 (VIN5), U11.3 (VIN6), U11.27 (VIN1), U11.28 (VIN2), U11.29 (VIN3), U14.18 (VP1), U14.23 (VP2)

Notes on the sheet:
JST Debug Connector
12MHz Crystal
Flash 4MB
-> TO TAD5112
CLASS D AMP Stage 47.5k / (3.3k+8.2k) = 4.05 V/V or 12.5dB
3.3V ---> 5V
-> TO HUB75
^ISNS^
Designed by Isaac Olson
-> TO PD CONTROLLER
OP AMP Stage 34.8k / 10k = 3.48V/V or 10.8dB Original TLC082 on ref design updated with TLV9162
EPR POWER MANAGEMENT
CONTROL
TAD5112 DAC
HUB75 DATA OUT + LEVEL SHIFTERS
HIGH CURRENT 5V POWER MANAGEMENT
V / I Sensing

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
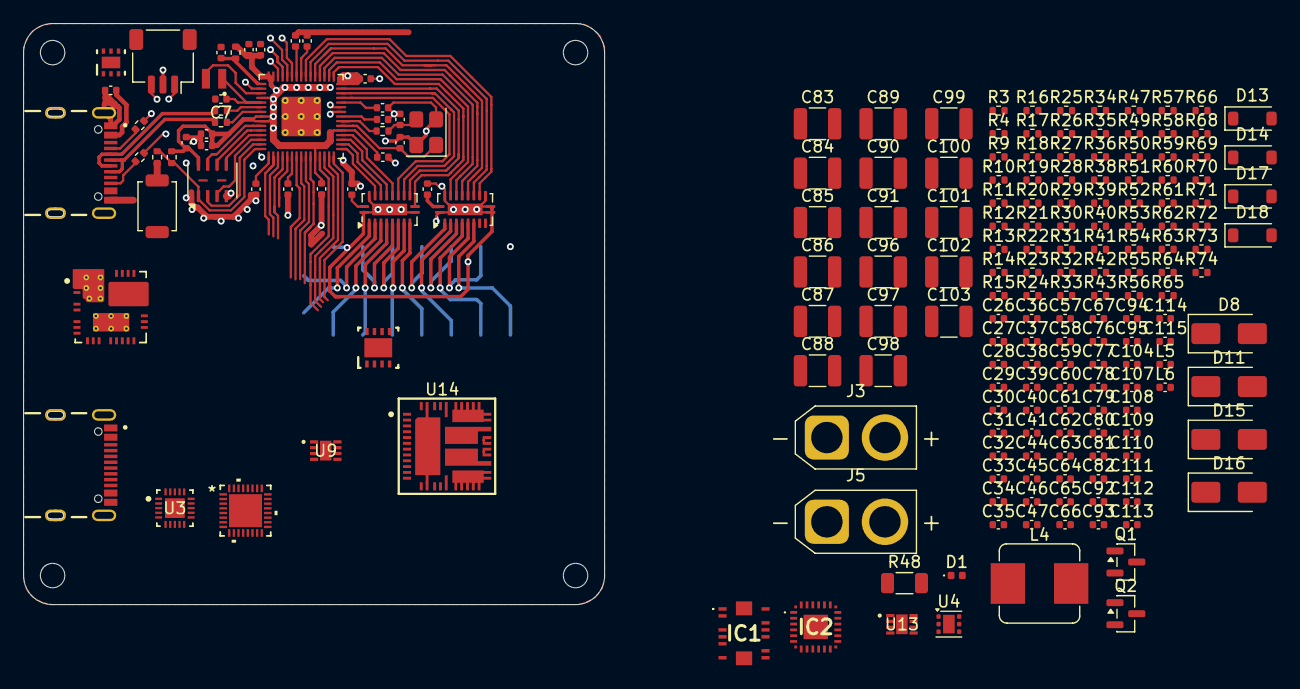
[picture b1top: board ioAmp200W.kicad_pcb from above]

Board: 6 copper layers, 50.0 x 50.0 mm, 203 parts (1 on the bottom side), 143 nets.

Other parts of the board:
R3#2, R4#2: 5.1k; R_0402_1005Metric

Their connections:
GND: R3#2.1, R4#2.1; also elsewhere on the board
unnamed 118: R4#2.2; also elsewhere on the board
unnamed 119: R3#2.2; also elsewhere on the board

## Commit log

2025-09-30 work
2025-10-09 switch_dsp
2025-10-11 compilable_firmware
2025-10-11 setup script
2025-10-11 verified_install_script
2025-10-11 ioAmp shows in windows and ios
2025-10-12 rp2040_compile_flag
2025-11-03 libs
2025-11-03 level_shift
2025-11-06 flash
2025-11-06 hub75
2025-11-11 codec
2026-02-17 start_amp
2026-03-01 btl_schem_copy
2026-03-11 dcdc
2026-03-18 wokr
2026-04-20 buck
2026-04-20 verifybuck
2026-05-20 summer_start
2026-05-27 DCbalance
2026-05-28 erroramp
2026-05-28 verify
2026-05-29 pffb
2026-05-29 isns
